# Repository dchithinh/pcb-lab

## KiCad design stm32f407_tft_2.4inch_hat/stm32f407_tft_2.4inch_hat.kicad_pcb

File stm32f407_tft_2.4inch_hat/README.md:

# stm32f407_tft_2.4inch_hat

KiCad project: a **plug-on HAT** for the **STM32F407 Discovery**.

Schematic and PCB only — no firmware in this repo.

## Board preview

### Assembled (real PCB + 2.4" LCD)

### KiCad 3D

Renders and photos live under `doc/` (`PCB.jpg`, `PCB_3D.png`).

## Goal

One board you can solder and plug onto the Discovery:

| Block | On the HAT |
|--------|------------|
| SPI display | 2.4" ILI9341: SCK, MOSI, MISO, CS, D/C, RST, LED |
| I2C | Shared bus, pull-ups, extra connector (Grove / 2.54" / Qwiic) for sensors (e.g. HDC1080) |
| USART A | Debug console header (USB–UART) |
| USART B | ESP32 TX/RX (plus RST, BOOT) — **unstuffed** on first spin is fine |
| Power | 3.3 V / GND from Discovery; ESP32 uses a **5 V → 3.3 V LDO** on the HAT |

## Net names (schematic = PCB)

| Use on schematic | PCB net | Notes |
|------------------|---------|--------|
| `GND` | `/GND` | |
| `3V` | `/3V` | 3.3 V on 1×4 headers |
| `5V` | `/5V` | Discovery 5 V |
| `VDD` | `/VDD` | Discovery 3.3 V pins (tie to `3V` on the schematic if one rail) |
| `DBG_UART2_TX`, `DBG_UART2_RX` | same | USART2 on **PA2 / PA3** (not USART1) |
| `I2C2_SCL`, `I2C2_SDA` | same | **PB10 / PB11** — not `I2C_SCL` / `I2C_SDA` |
| `LCD_*` | same | Display, touch, SD, SPI2 (see signal table below) |

### HAT connectors (PCB)

- **`DBG_UART1`** (1×4): 1 `3V`, 2 `DBG_UART2_RX`, 3 `DBG_UART2_TX`, 4 `GND`
- **`I2C-Sensor1`** / **`I2C-RealTime1`** (1×4): 1 `I2C2_SCL`, 2 `I2C2_SDA`, 3 `3V`, 4 `GND`

### HAT signal pins (schematic labels)

| Function | Connector | Pad | MCU | Net |
|----------|-----------|-----|-----|-----|
| USART2 debug | P2 | 13 | PA2 | `DBG_UART2_TX` |
| USART2 debug | P2 | 14 | PA3 | `DBG_UART2_RX` |
| I2C2 sensor bus | P2 | 33 | PB10 | `I2C2_SCL` |
| I2C2 sensor bus | P2 | 36 | PB11 | `I2C2_SDA` |
| SPI2 display | P2 | 38 | PB13 | `LCD_SCK` |
| SPI2 display | P2 | 40 | PB15 | `LCD_MOSI` |
| SPI2 display | P2 | 9 | PC2 | `LCD_MISO` |
| LCD control | P2 | 41 | PD10 | `LCD_RESET` |
| LCD control | P2 | 42 | PD9 | `LCD_DC` |
| LCD chip select | P1 | 19 | PB9 | `LCD_CS` |
| SPI3 SD / touch (shared CLK/MOSI/MISO) | P1 | 38 | PC10 | `LCD_SD_CLK` |
| SPI3 SD / touch | P1 | 37 | PC11 | `LCD_SD_MISO` |
| SPI3 SD / touch | P1 | 36 | PC12 | `LCD_SD_MOSI` |
| Touch / SD chip selects | P1 | 15 | PE3 | `LCD_T_CS` |
| Touch / SD chip selects | P1 | 14 | PE4 | `LCD_SD_CS` |
| Touch IRQ | P1 | 12 | PE5 | `LCD_T_IRQ` |

On the ILI9341 module, touch and SD share SPI lines; the schematic uses `LCD_SD_*` / `LCD_T_*` aliases on the same nets where noted in KiCad.

## Files

| File | Role |
|------|------|
| `stm32f407_tft_2.4inch_hat.kicad_pro` | Project |
| `stm32f407_tft_2.4inch_hat.kicad_sch` | Schematic |
| `stm32f407_tft_2.4inch_hat.kicad_pcb` | Board |
| `stm32f407_tft_2.7inch_hat_gerber_v1/` | Gerber release + `schematic_v1.pdf` |
| `doc/PCB.jpg` | Assembled HAT with 2.4" LCD (see preview above) |
| `doc/PCB_3D.png` | KiCad 3D board render (see preview above) |

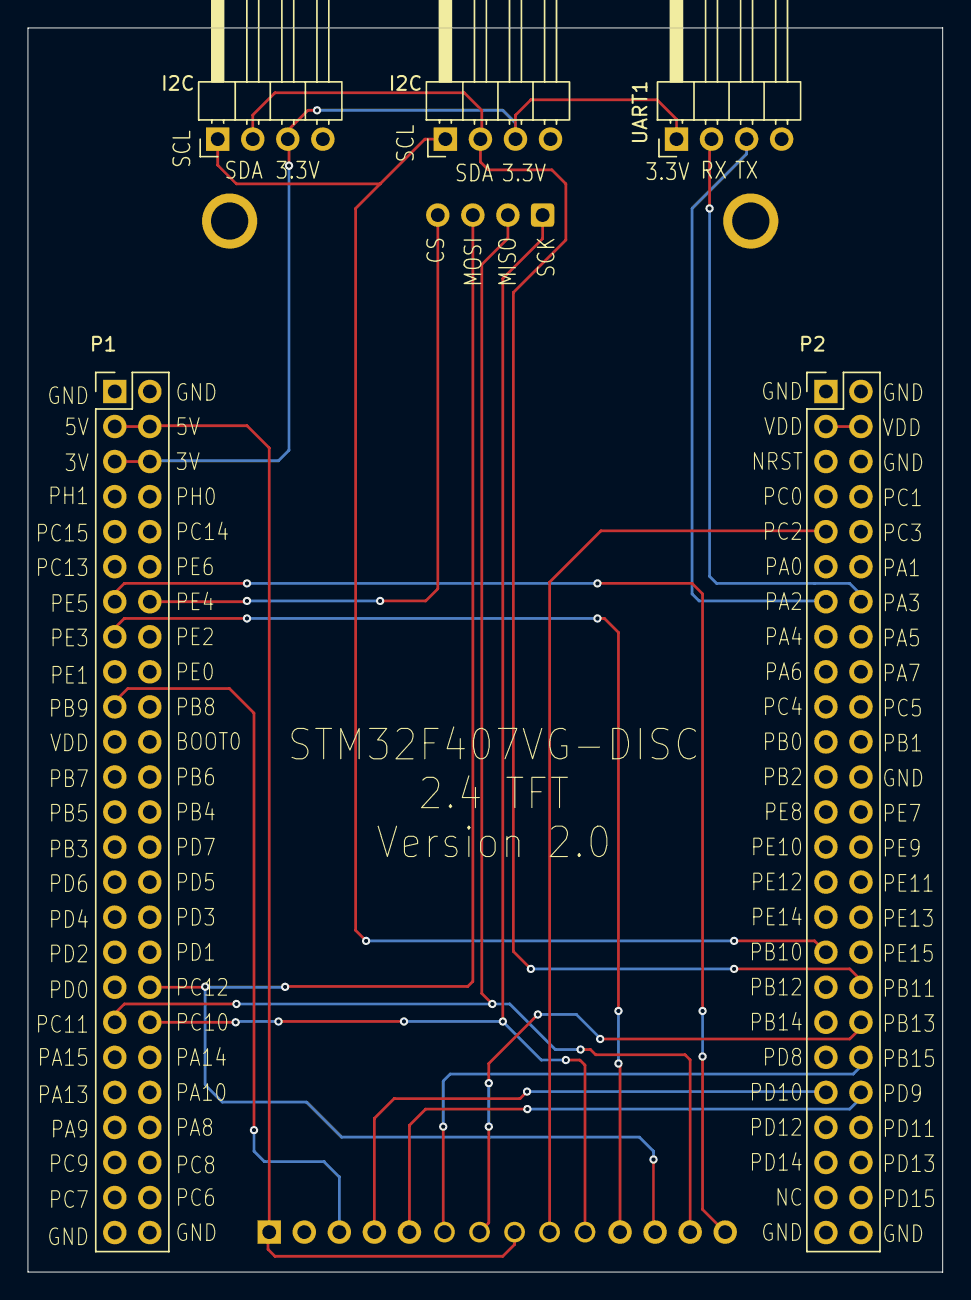
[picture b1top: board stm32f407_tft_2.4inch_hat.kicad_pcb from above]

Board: 2 copper layers, 66.3 x 90.2 mm, 6 parts (0 on the bottom side), 20 nets.

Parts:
I2C, I2C#2: Conn_01x04_Pin; PinHeader_1x04_P2.54mm_Horizontal
LCD_Panel1: TFT SPI 240x320; CR2013-MI2120
P1: STM32F407-DISC P1; PinHeader_2x25_P2.54mm_Vertical
P2: STM32F407-DISC P2; PinHeader_2x25_P2.54mm_Vertical
UART1: Conn_01x04_Pin; PinHeader_1x04_P2.54mm_Horizontal

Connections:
/3V: I2C.3, I2C#2.3, P1.5 (3V), P1.6 (3V), UART1.1
/5V: LCD_Panel1.1 (VCC), LCD_Panel1.8 (LED), P1.3 (5V), P1.4 (5V)
/DBG_UART2_RX: P2.14 (PA3), UART1.2
/DBG_UART2_TX: P2.13 (PA2), UART1.3
/GND: I2C.4, I2C#2.4, LCD_Panel1.2 (GND), P1.1 (GND), P1.2 (GND), P1.49 (GND), P1.50 (GND), P2.1 (GND), P2.2 (GND), P2.6 (GND), P2.24 (GND), P2.49 (GND), P2.50 (GND), UART1.4
/I2C2_SCL: I2C.1, I2C#2.1, P2.33 (PB10)
/I2C2_SDA: I2C.2, I2C#2.2, P2.36 (PB11)
/LCD_CS: LCD_Panel1.3 (~CS), P1.19 (PB8)
/LCD_DC: LCD_Panel1.5 (D/~C), P2.42 (PD9)
/LCD_MISO: LCD_Panel1.9 (MISO), P2.9 (PC2)
/LCD_MOSI: LCD_Panel1.6 (MOSI), P2.40 (PB15)
/LCD_RESET: LCD_Panel1.4 (RESET), P2.41 (PD10)
/LCD_SCK: LCD_Panel1.7 (SCK), P2.38 (PB13)
/LCD_SD_CLK: LCD_Panel1.10 (T_CLK), LCD_Panel1.15 (SD_CLK), P1.38 (PA15)
/LCD_SD_CS: LCD_Panel1.18 (SD_CS), P1.14 (PE3)
/LCD_SD_MISO: LCD_Panel1.13 (T_MISO), LCD_Panel1.16 (SD_MISO), P1.37 (PC10)
/LCD_SD_MOSI: LCD_Panel1.12 (T_MOSI), LCD_Panel1.17 (SD_MOSI), P1.36 (PC11)
/LCD_T_CS: LCD_Panel1.11 (T_CS), P1.15 (PE2)
/LCD_T_IRQ: LCD_Panel1.14 (T_IRQ), P1.13 (PE4)
/VDD: P2.3 (VDD), P2.4 (VDD)
